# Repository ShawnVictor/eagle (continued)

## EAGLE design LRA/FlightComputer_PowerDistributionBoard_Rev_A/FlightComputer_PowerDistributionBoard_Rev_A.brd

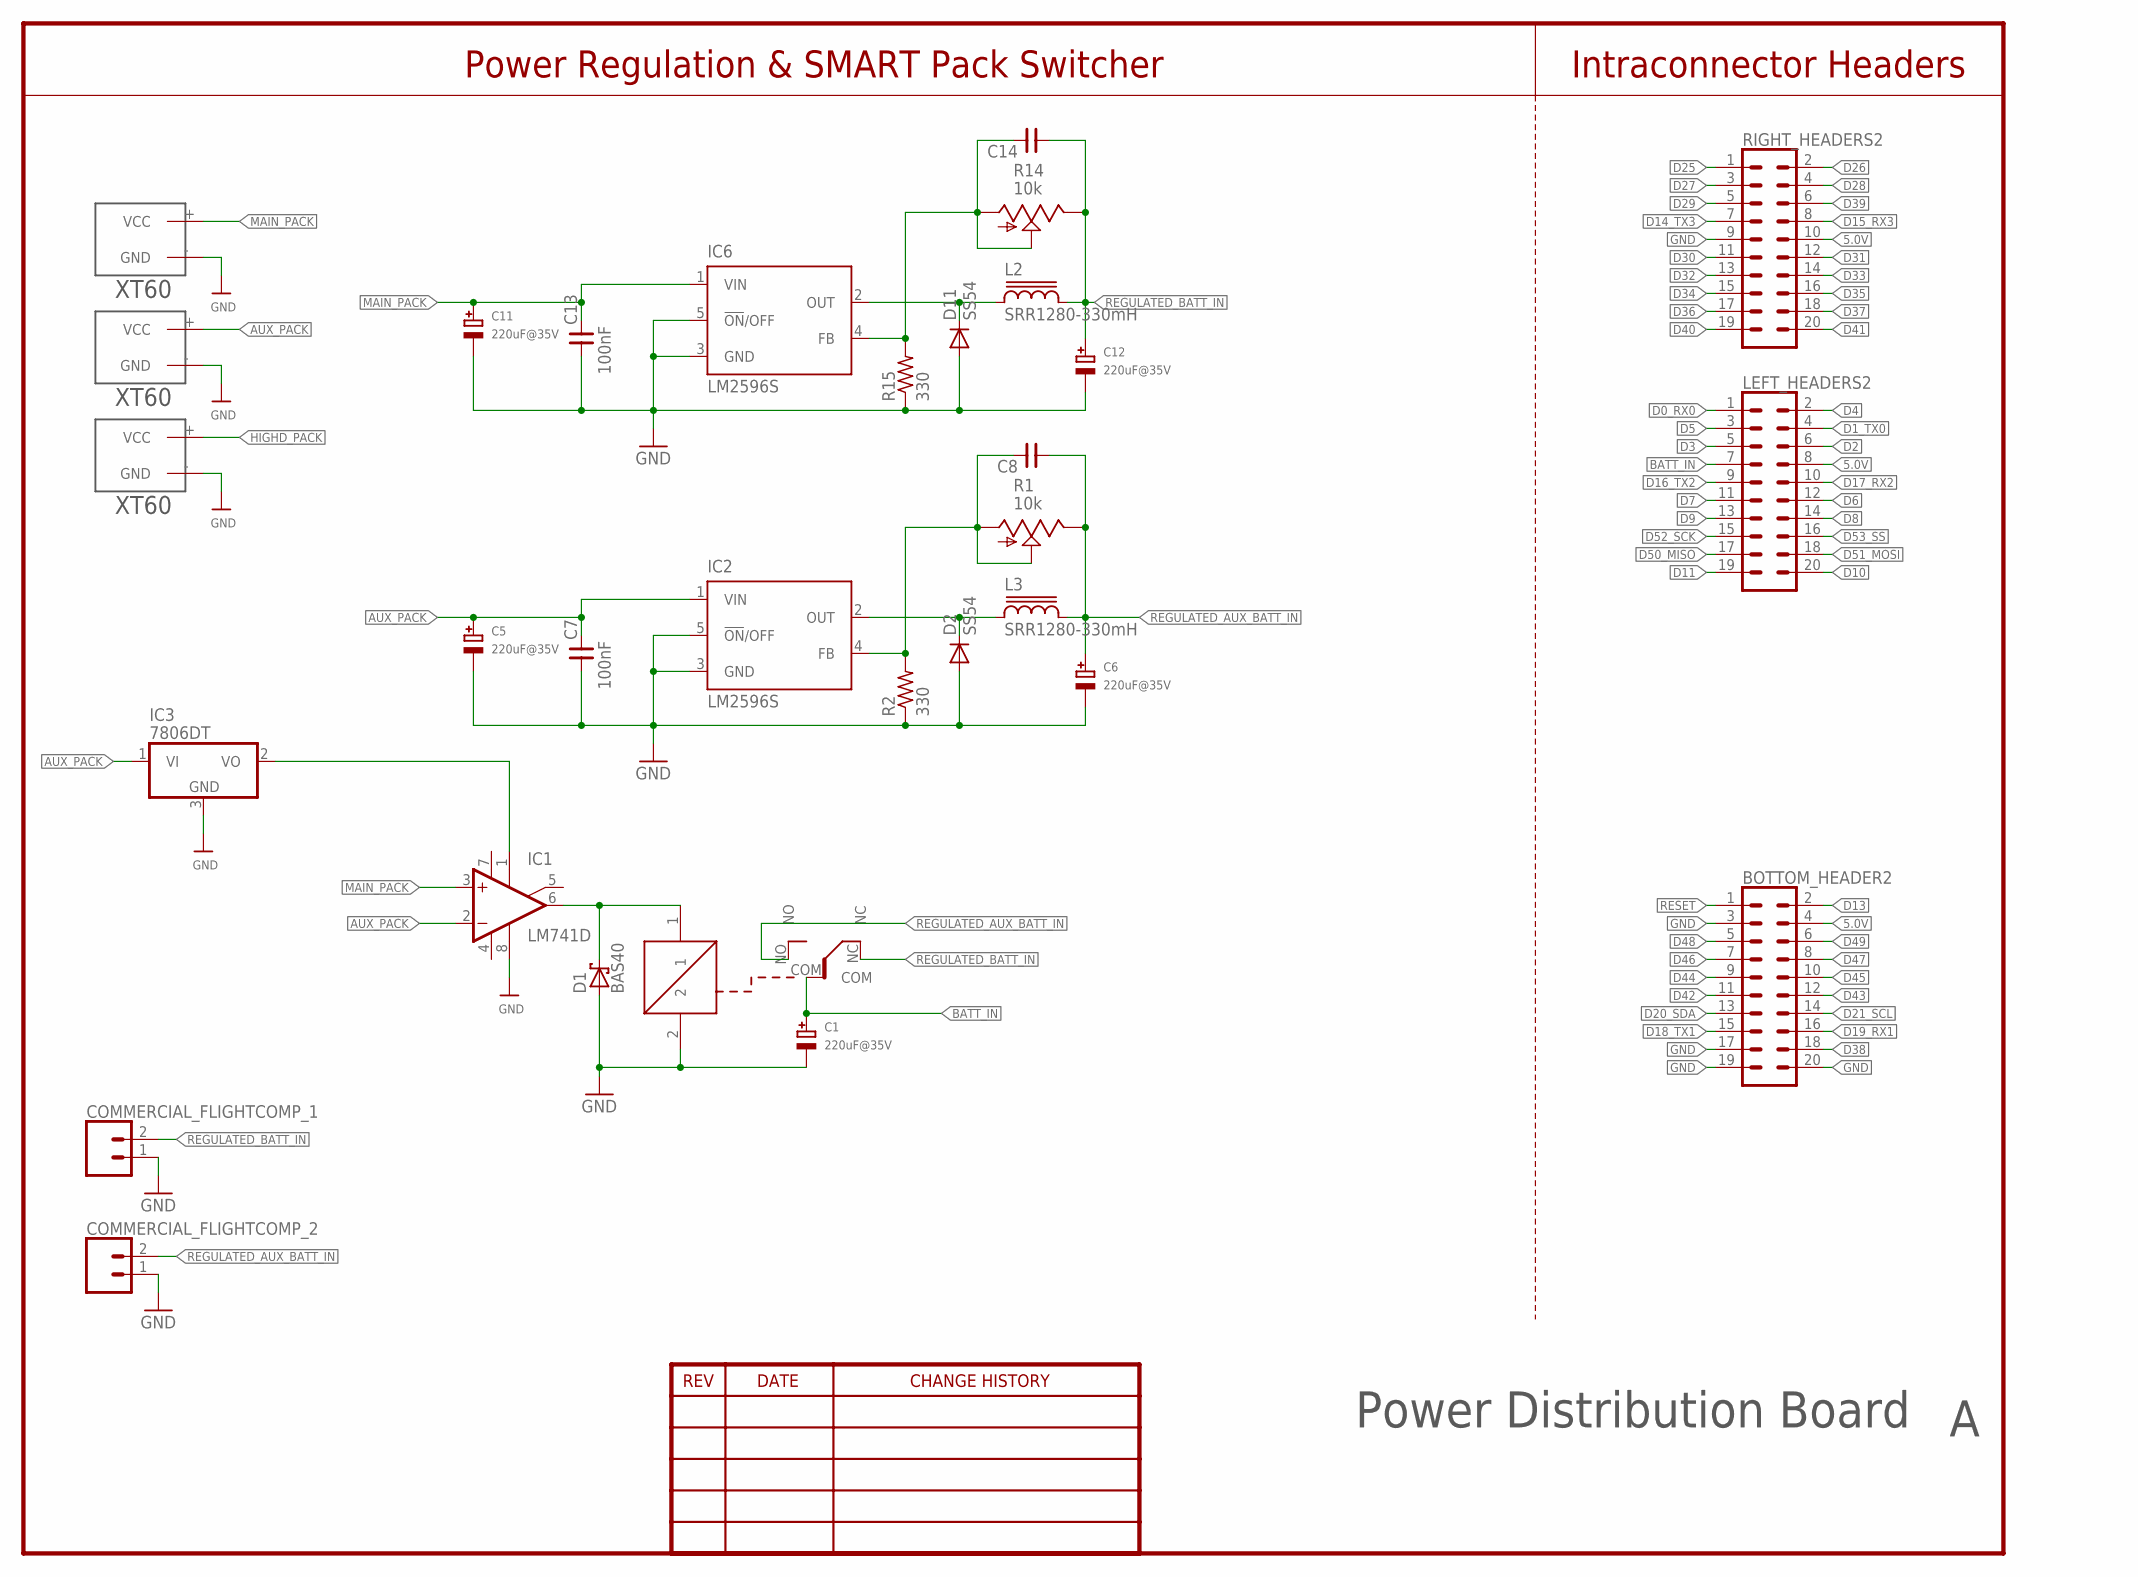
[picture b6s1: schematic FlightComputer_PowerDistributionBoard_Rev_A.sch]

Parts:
BOTTOM_HEADER2: CONN_10X2; 2X10
C1, C5, C6, C11, C12: 220uF@35V; PANASONIC_D
C7, C13: 100nF; 0603
C8, C14: CNP-0603; 0603
COMMERCIAL_FLIGHTCOMP_1, COMMERCIAL_FLIGHTCOMP_2: CONN_02; 1X02
D1: BAS40; SOT23
D2, D11: SS54; DO214AB
IC1: LM741D; SO08
IC2, IC6: LM2596S; TO263-5
IC3: 7806DT; TO252
L2, L3: SRR1280-330mH; SRR1280
LEFT_HEADERS2: CONN_10X2; 2X10
R1, R14: 10k; S64W
R2, R15: 330; R0603
RIGHT_HEADERS2: CONN_10X2; 2X10
U$2, U$3, U$4: XT60
U$14: RW-SH

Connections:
5.0V: BOTTOM_HEADER2.4, LEFT_HEADERS2.8, RIGHT_HEADERS2.10
AUX_PACK: C5.+, C7.2, IC1.2 (-IN), IC2.1 (VIN), IC3.1 (VI), U$3.+ (VCC)
BATT_IN: C1.+, LEFT_HEADERS2.7, U$14.COM
D0_RX0: LEFT_HEADERS2.1
D1_TX0: LEFT_HEADERS2.4
D2: LEFT_HEADERS2.6
D3: LEFT_HEADERS2.5
D4: LEFT_HEADERS2.2
D5: LEFT_HEADERS2.3
D6: LEFT_HEADERS2.12
D7: LEFT_HEADERS2.11
D8: LEFT_HEADERS2.14
D9: LEFT_HEADERS2.13
D10: LEFT_HEADERS2.20
D11: LEFT_HEADERS2.19
D13: BOTTOM_HEADER2.2
D14_TX3: RIGHT_HEADERS2.7
D15_RX3: RIGHT_HEADERS2.8
D16_TX2: LEFT_HEADERS2.9
D17_RX2: LEFT_HEADERS2.10
D18_TX1: BOTTOM_HEADER2.15
D19_RX1: BOTTOM_HEADER2.16
D20_SDA: BOTTOM_HEADER2.13
D21_SCL: BOTTOM_HEADER2.14
D25: RIGHT_HEADERS2.1
D26: RIGHT_HEADERS2.2
D27: RIGHT_HEADERS2.3
D28: RIGHT_HEADERS2.4
D29: RIGHT_HEADERS2.5
D30: RIGHT_HEADERS2.11
D31: RIGHT_HEADERS2.12
D32: RIGHT_HEADERS2.13
D33: RIGHT_HEADERS2.14
D34: RIGHT_HEADERS2.15
D35: RIGHT_HEADERS2.16
D36: RIGHT_HEADERS2.17
D37: RIGHT_HEADERS2.18
D38: BOTTOM_HEADER2.18
D39: RIGHT_HEADERS2.6
D40: RIGHT_HEADERS2.19
D41: RIGHT_HEADERS2.20
D42: BOTTOM_HEADER2.11
D43: BOTTOM_HEADER2.12
D44: BOTTOM_HEADER2.9
D45: BOTTOM_HEADER2.10
D46: BOTTOM_HEADER2.7
D47: BOTTOM_HEADER2.8
D48: BOTTOM_HEADER2.5
D49: BOTTOM_HEADER2.6
D50_MISO: LEFT_HEADERS2.17
D51_MOSI: LEFT_HEADERS2.18
D52_SCK: LEFT_HEADERS2.15
D53_SS: LEFT_HEADERS2.16
GND: BOTTOM_HEADER2.3, BOTTOM_HEADER2.17, BOTTOM_HEADER2.19, BOTTOM_HEADER2.20, C1.-, C5.-, C6.-, C7.1, C11.-, C12.-, C13.1, COMMERCIAL_FLIGHTCOMP_1.1, COMMERCIAL_FLIGHTCOMP_2.1, D1.1 (A), D2.A, D11.A, IC1.8 (OPT), IC2.3 (GND), IC2.5 (!ON!/OFF), IC3.3 (GND), IC6.3 (GND), IC6.5 (!ON!/OFF), R2.1, R15.1, RIGHT_HEADERS2.9, U$2.- (GND), U$3.- (GND), U$4.- (GND), U$14.2
HIGHD_PACK: U$4.+ (VCC)
MAIN_PACK: C11.+, C13.2, IC1.3 (+IN), IC6.1 (VIN), U$2.+ (VCC)
unnamed: D2.C, IC2.2 (OUT), L3.1
unnamed: C8.2, IC2.4 (FB), R1.A, R1.S, R2.2
unnamed: IC1.1 (ON1), IC3.2 (VO)
unnamed: D1.3 (C), IC1.6 (OUT), U$14.1
unnamed: D11.C, IC6.2 (OUT), L2.1
unnamed: C14.2, IC6.4 (FB), R14.A, R14.S, R15.2
REGULATED_AUX_BATT_IN: C6.+, C8.1, COMMERCIAL_FLIGHTCOMP_2.2, L3.2, R1.E, U$14.NO
REGULATED_BATT_IN: C12.+, C14.1, COMMERCIAL_FLIGHTCOMP_1.2, L2.2, R14.E, U$14.NC
RESET: BOTTOM_HEADER2.1
V+: IC1.7 (V+)
V-: IC1.4 (V-)

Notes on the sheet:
Intraconnector Headers
Power Regulation & SMART Pack Switcher
Power Distribution Board

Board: 2 copper layers, 31 parts (0 on the bottom side), 13 nets, no tracks yet.

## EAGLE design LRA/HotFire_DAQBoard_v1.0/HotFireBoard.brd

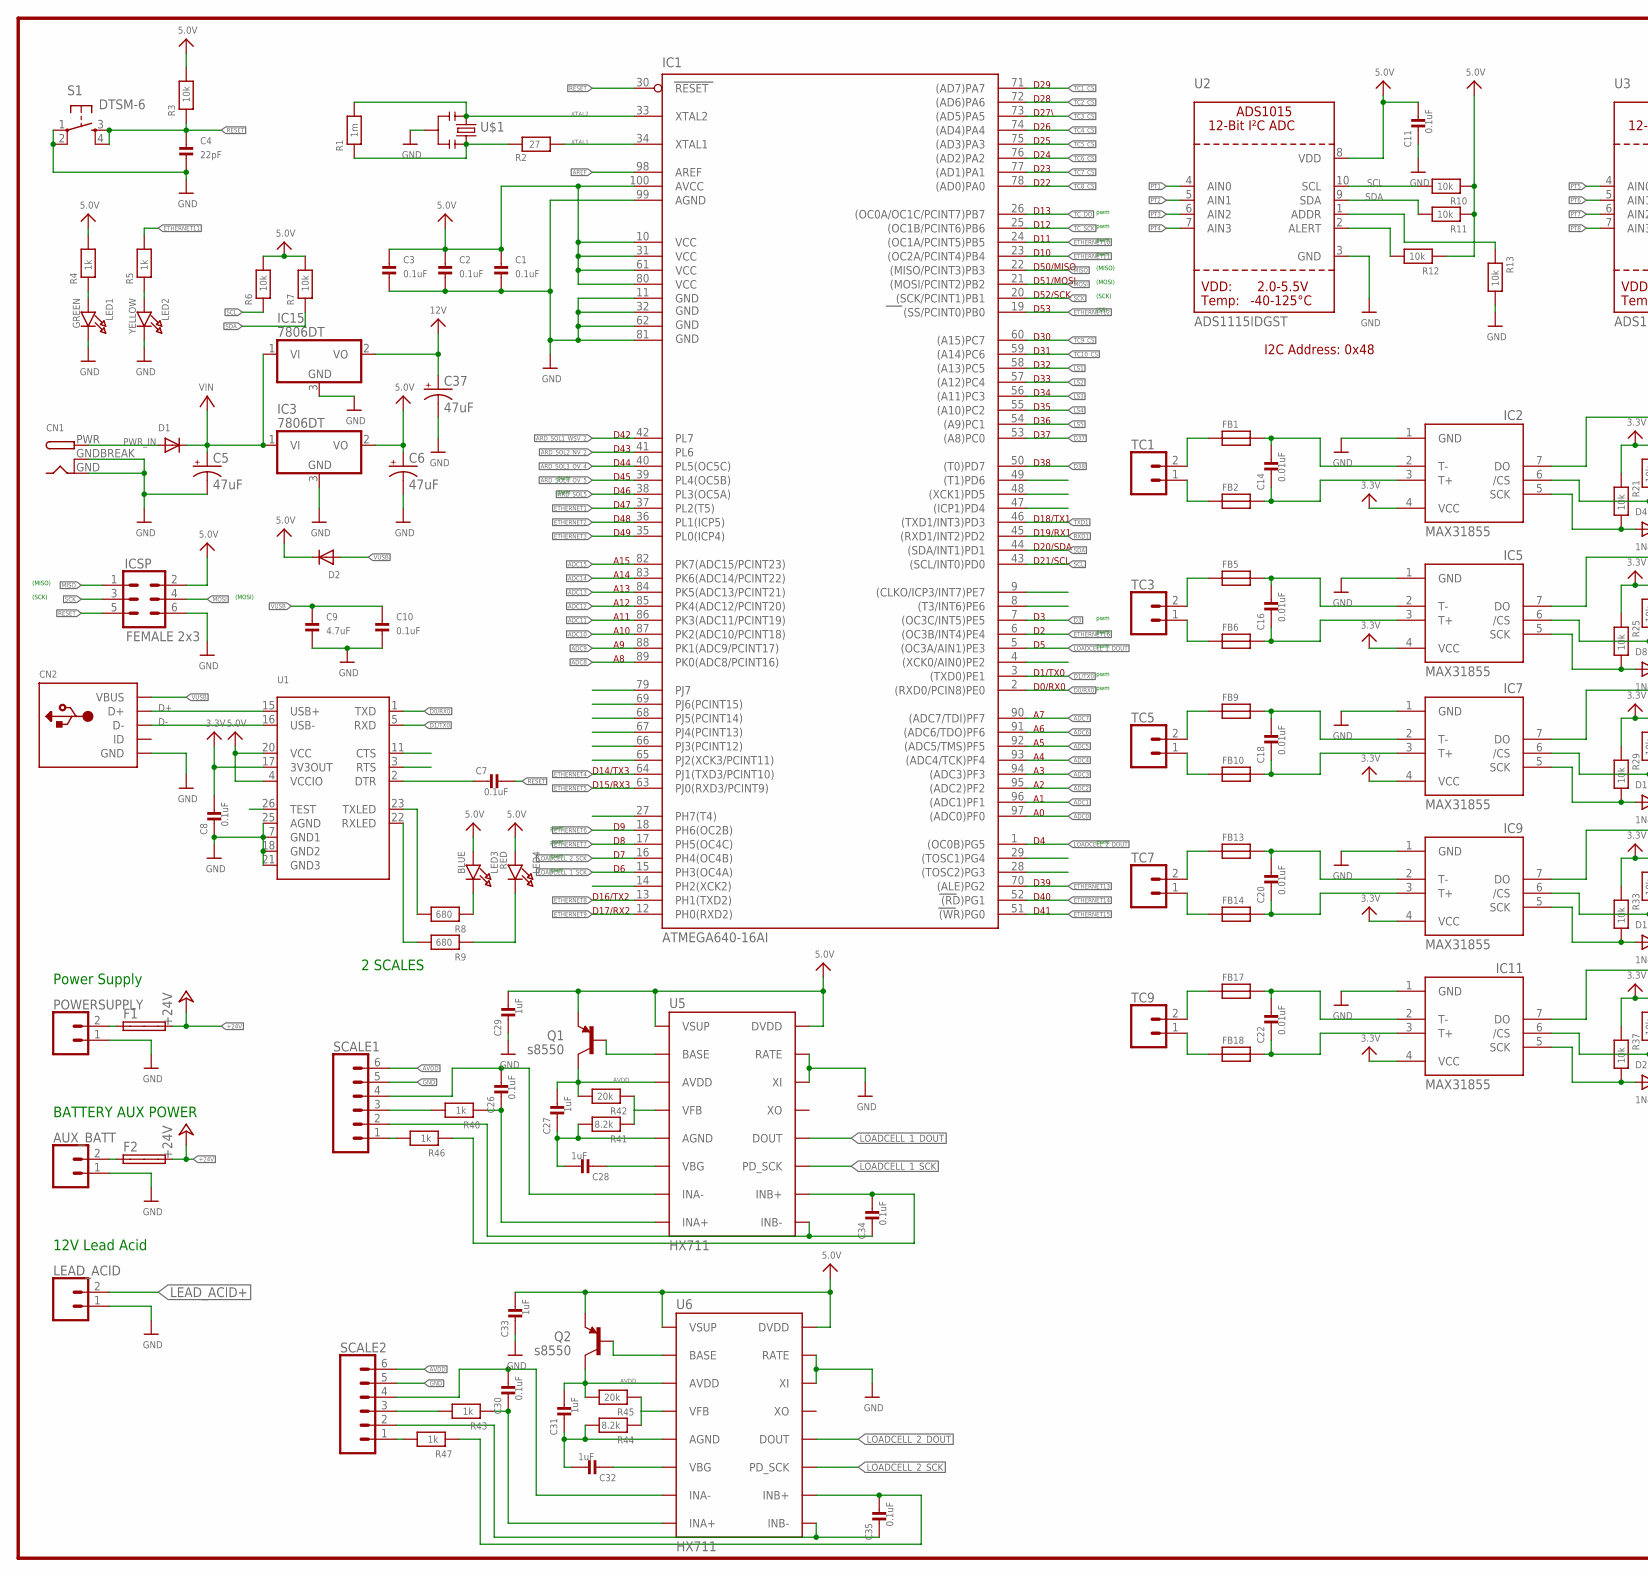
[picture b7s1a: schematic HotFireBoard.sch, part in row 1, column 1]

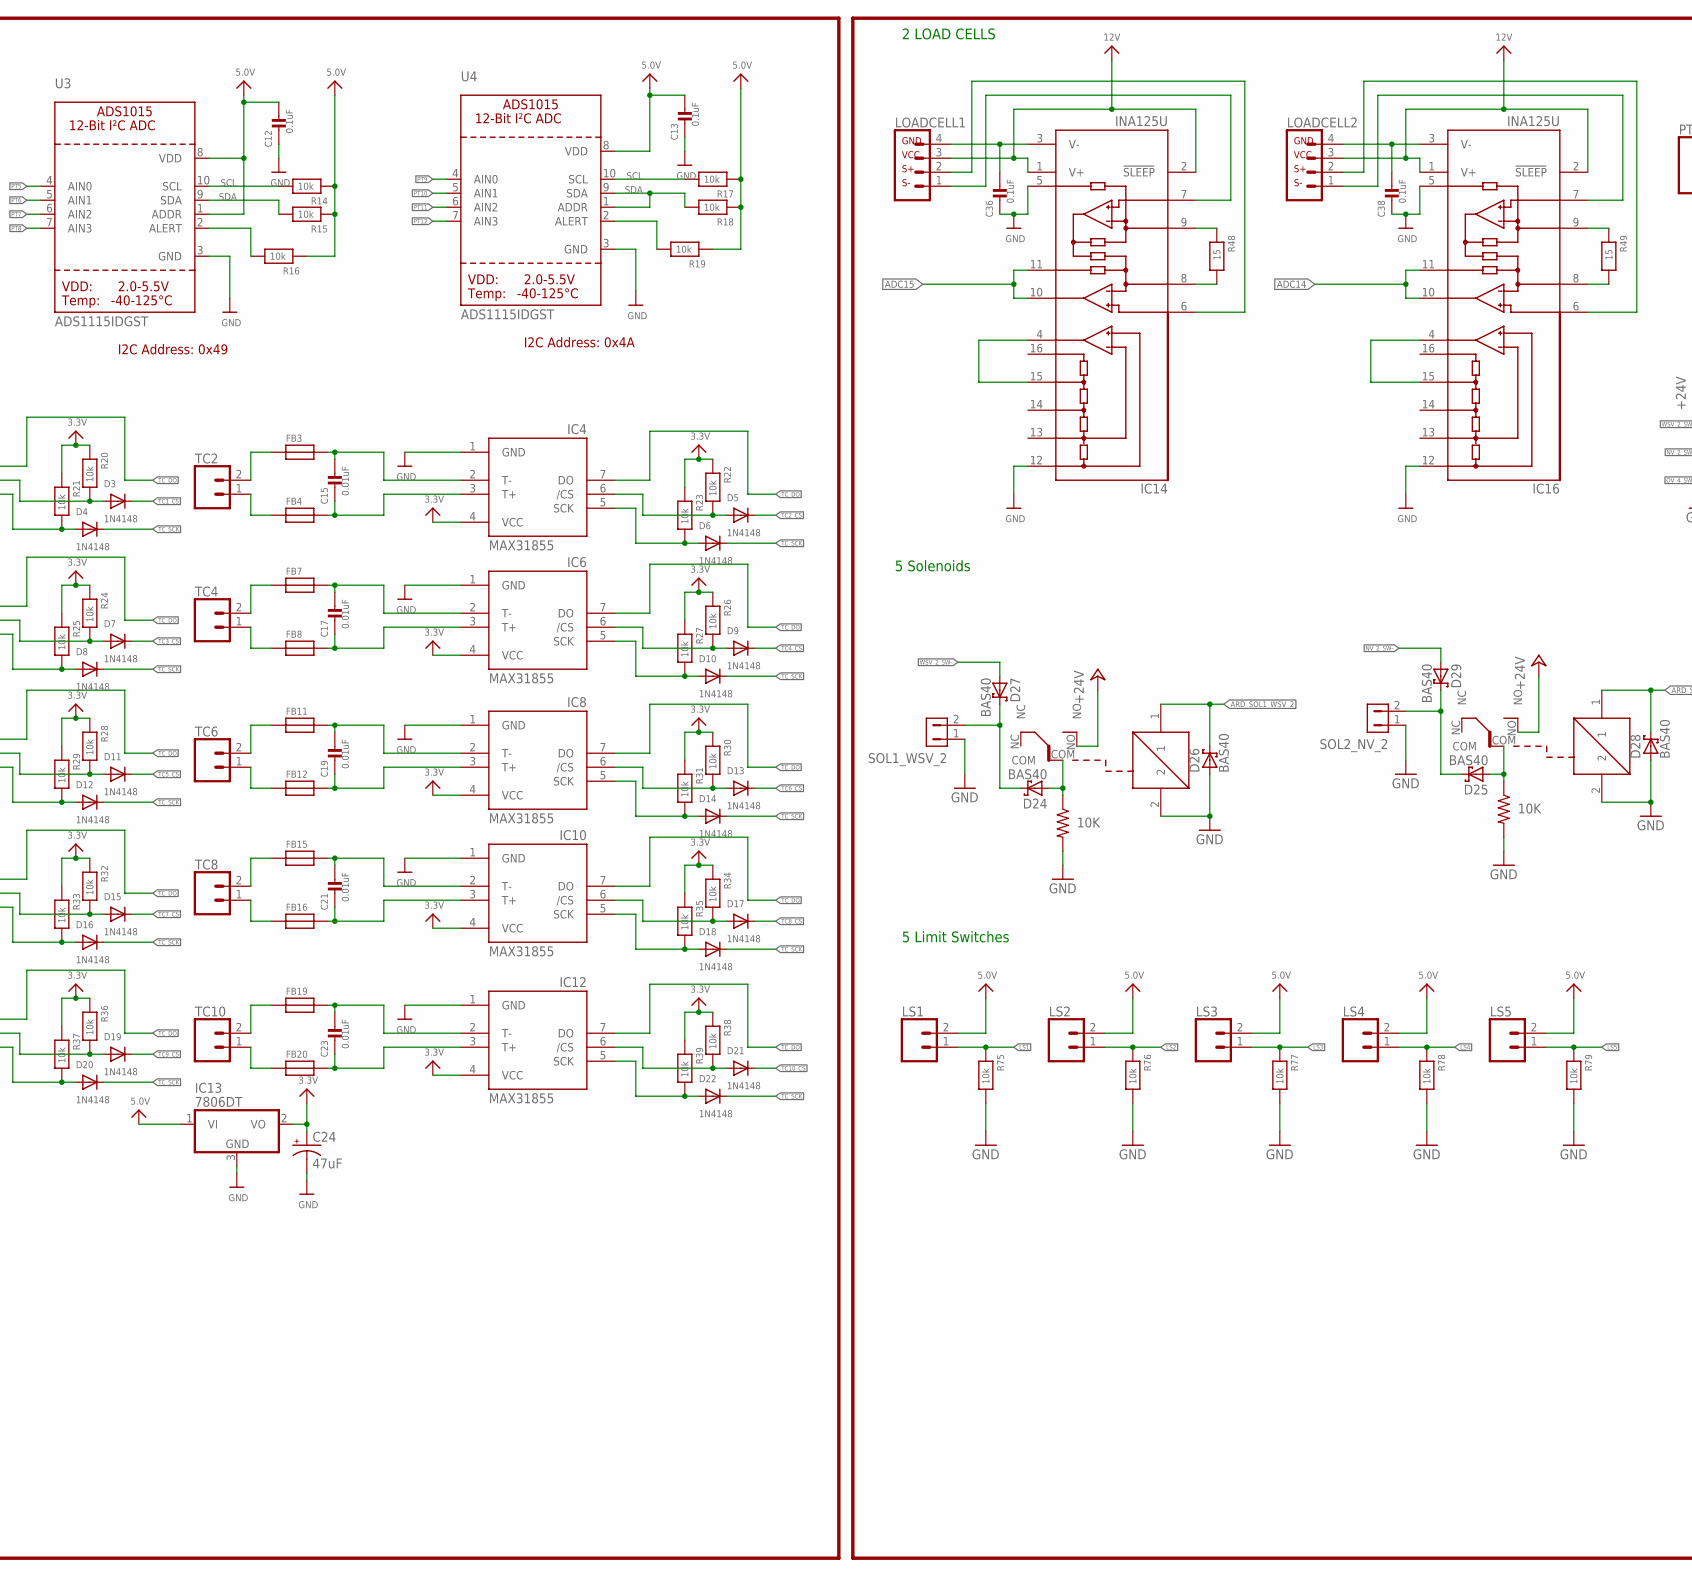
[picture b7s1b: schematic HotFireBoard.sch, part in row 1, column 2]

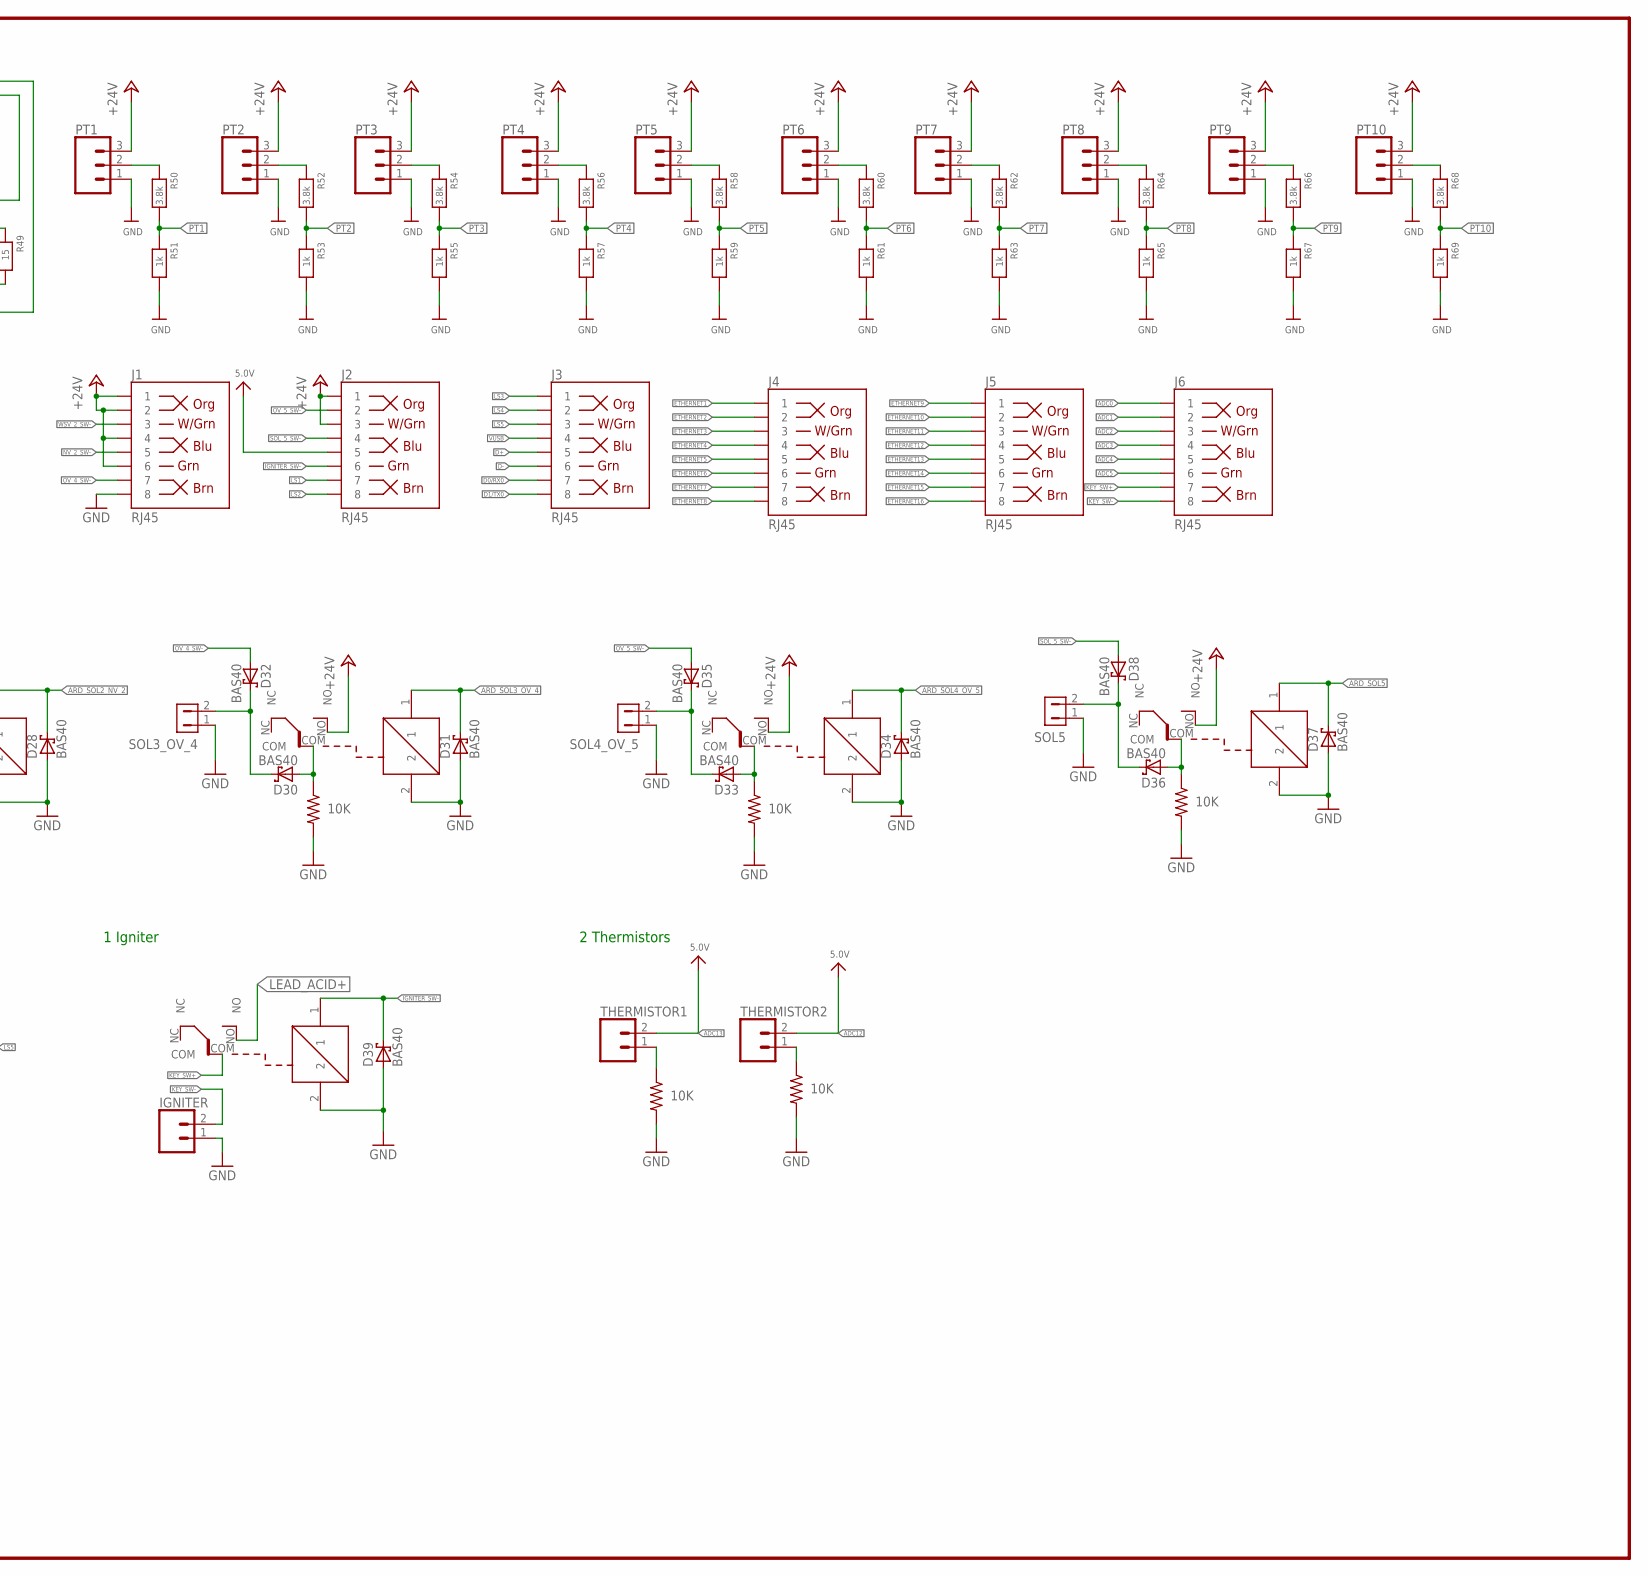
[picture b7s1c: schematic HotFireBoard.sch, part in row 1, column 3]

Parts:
AUX_BATT: CONN_02; 1X02
C1, C2, C3, C7, C8, C10, C11, C12, C13, C26, C30, C34, C35, C36, C38: 0.1uF; 0805
C4: 22pF; 0805
C5, C6, C24, C37: 47uF; PANASONIC_D
C9: 4.7uF; 0805
C14, C15, C16, C17, C18, C19, C20, C21, C22, C23: 0.01uF; 0805
C27, C28, C29, C31, C32, C33: 1uF; 0805
CN1: DCBARRELPTH; DCJACK_2MM_PTH
CN2: USBMINIB; USB-MINIB
D1, D2: DIODESOD-123; SOD-123
D3, D4, D5, D6, D7, D8, D9, D10, D11, D12, D13, D14, D15, D16, D17, D18, D19, D20, D21, D22: 1N4148; SOD-123
D24, D25, D26, D27, D28, D29, D30, D31, D32, D33, D34, D35, D36, D37, D38, D39: BAS40; SOT23
F1, F2: SHK20L
FB1, FB2, FB3, FB4, FB5, FB6, FB7, FB8, FB9, FB10, FB11, FB12, FB13, FB14, FB15, FB16, FB17, FB18, FB19, FB20: FERRITE; 0603
IC1: ATMEGA640-16AI; TQFP100
IC2, IC4, IC5, IC6, IC7, IC8, IC9, IC10, IC11, IC12: MAX31855; SO08
IC3, IC13, IC15: 7806DT; TO252
IC14, IC16: INA125U; SO16-1
ICSP: FEMALE 2x3; 2X3
IGNITER: CONN_025MM; SCREWTERMINAL-5MM-2
J1, J2, J3, J4, J5, J6: RJ45; RJ45-8
LEAD_ACID: CONN_02; 1X02
LED1: GREEN; CHIPLED_0805
LED2: YELLOW; CHIPLED_0805
LED3: BLUE; CHIPLED_0805
LED4: RED; CHIPLED_0805
LOADCELL1, LOADCELL2: CONN_04; 1X04
LS1, LS2, LS3, LS4, LS5: CONN_02; 1X02
POWERSUPPLY: CONN_02; 1X02
PT1, PT2, PT3, PT4, PT5, PT6, PT7, PT8, PT9, PT10: CONN_03; 1X03
Q1, Q2: s8550; TO-92
R1: 1m; 0805
R2: 27; 0805
R3, R6, R7, R10, R11, R12, R13, R14, R15, R16, R17, R18, R19, R20, R21, R22, R23, R24, R25, R26, R27, R28, R29, R30, R31, R32, R33, R34, R35, R36, R37, R38, R39, R75, R76, R77, R78, R79: 10k; 0805
R4, R5, R40, R43, R46, R47, R51, R53, R55, R57, R59, R61, R63, R65, R67, R69: 1k; 0805
R8, R9: 680; 0805
R41, R44: 8.2k; 0805
R42, R45: 20k; 0805
R48, R49: 15; 0805
R50, R52, R54, R56, R58, R60, R62, R64, R66, R68: 3.8k; 0805
R70, R71, R72, R73, R74, R80, R81: 10K; M0805
S1: DTSM-6
SCALE1, SCALE2: CONN_06SILK_FEMALE_PTH; 1X06
SOL1_WSV_2, SOL2_NV_2, SOL3_OV_4, SOL4_OV_5, SOL5: HDR-1X2-MTA-100; MTA-100-2V
TC1, TC2, TC3, TC4, TC5, TC6, TC7, TC8, TC9, TC10: CONN_02; 1X02
THERMISTOR1, THERMISTOR2: CONN_02; 1X02
U1: FT232RLSSOP28; SSOP28DB
U2, U3, U4: ADS1115IDGST; MSOP10
U5, U6: HX711; SO16
U$1: RESONATORSMD; RESONATOR-SMD
U$128, U$129, U$130, U$131, U$132, U$138: RW-SH

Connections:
3.3V: C8.2, C24.+, IC2.4 (VCC), IC4.4 (VCC), IC5.4 (VCC), IC6.4 (VCC), IC7.4 (VCC), IC8.4 (VCC), IC9.4 (VCC), IC10.4 (VCC), IC11.4 (VCC), IC12.4 (VCC), IC13.2 (VO), R20.1, R21.1, R22.1, R23.1, R24.1, R25.1, R26.1, R27.1, R28.1, R29.1, R30.1, R31.1, R32.1, R33.1, R34.1, R35.1, R36.1, R37.1, R38.1, R39.1, U1.17 (3V3OUT)
5.0V: C1.1, C2.1, C3.1, C6.+, C11.2, C12.2, C13.2, C29.2, C33.2, D2.C, IC1.10 (VCC), IC1.31 (VCC1), IC1.61 (VCC2), IC1.80 (VCC3), IC1.100 (AVCC), IC3.2 (VO), IC13.1 (VI), ICSP.2, J2.5, LED3.A, LED4.A, LS1.2, LS2.2, LS3.2, LS4.2, LS5.2, Q1.1 (E), Q2.1 (E), R3.2, R4.2, R6.2, R7.2, R10.1, R11.1, R12.1, R14.1, R15.1, R16.1, R17.1, R18.1, R19.1, U1.4 (VCCIO), U1.20 (VCC), U2.8 (VDD), U3.1 (ADDR), U3.8 (VDD), U4.8 (VDD), U5.1 (VSUP), U5.16 (DVDD), U6.1 (VSUP), U6.16 (DVDD)
12V: C37.+, IC14.1 (V+), IC14.2 (!SLEEP), IC15.2 (VO), IC16.1 (V+), IC16.2 (!SLEEP), LOADCELL1.3, LOADCELL2.3
+24V: F1.2A, F2.2A, J1.1, J1.2, J1.4, J1.6, J2.1, J2.3, PT1.3, PT2.3, PT3.3, PT4.3, PT5.3, PT6.3, PT7.3, PT8.3, PT9.3, PT10.3, U$128.NO, U$129.NO, U$130.NO, U$131.NO, U$132.NO
ADC0: IC1.97 ((ADC0)PF0), J6.1
ADC1: IC1.96 ((ADC1)PF1), J6.2
ADC2: IC1.95 ((ADC2)PF2), J6.3
ADC3: IC1.94 ((ADC3)PF3), J6.4
ADC4: IC1.93 ((ADC4/TCK)PF4), J6.5
ADC5: IC1.92 ((ADC5/TMS)PF5), J6.6
ADC6: IC1.91 ((ADC6/TDO)PF6)
ADC7: IC1.90 ((ADC7/TDI)PF7)
ADC8: IC1.89 (PK0(ADC8/PCINT16))
ADC9: IC1.88 (PK1(ADC9/PCINT17))
ADC10: IC1.87 (PK2(ADC10/PCINT18))
ADC11: IC1.86 (PK3(ADC11/PCINT19))
ADC12: IC1.85 (PK4(ADC12/PCINT20)), THERMISTOR2.2
ADC13: IC1.84 (PK5(ADC13/PCINT21)), THERMISTOR1.2
ADC14: IC1.83 (PK6(ADC14/PCINT22)), IC16.10 (OUT), IC16.11 (SENSE)
ADC15: IC1.82 (PK7(ADC15/PCINT23)), IC14.10 (OUT), IC14.11 (SENSE)
ARD_SOL1_WSV_2: D26.3 (C), IC1.42 (PL7), U$128.1
ARD_SOL2_NV_2: D28.3 (C), IC1.41 (PL6), U$129.1
ARD_SOL3_OV_4: D31.3 (C), IC1.40 (PL5(OC5C)), U$130.1
ARD_SOL4_OV_5: D34.3 (C), IC1.39 (PL4(OC5B)), U$131.1
ARD_SOL5: D37.3 (C), IC1.38 (PL3(OC5A)), U$132.1
AREF: IC1.98 (AREF)
AVDD: C27.2, C31.2, Q1.3 (C), Q2.3 (C), R42.2, R45.2, SCALE1.6, SCALE2.6, U5.3 (AVDD), U6.3 (AVDD)
D0/RX0: IC1.2 ((RXD0/PCIN8)PE0), J3.7, U1.1 (TXD)
D1/TX0: IC1.3 ((TXD0)PE1), J3.8, U1.5 (RXD)
D3: IC1.7 ((OC3C/INT5)PE5)
D37: IC1.53 ((A8)PC0)
D38: IC1.50 ((T0)PD7)
D+: CN2.D+, J3.5, U1.15 (USB+)
D-: CN2.D-, J3.6, U1.16 (USB-)
ETHERNET1: IC1.37 (PL2(T5)), J4.1
ETHERNET2: IC1.36 (PL1(ICP5)), J4.2
ETHERNET3: IC1.35 (PL0(ICP4)), J4.3
ETHERNET4: IC1.64 (PJ1(TXD3/PCINT10)), J4.4
ETHERNET5: IC1.63 (PJ0(RXD3/PCINT9)), J4.5
ETHERNET6: IC1.18 (PH6(OC2B)), J4.6
ETHERNET7: IC1.17 (PH5(OC4C)), J4.7
ETHERNET8: IC1.13 (PH1(TXD2)), J4.8
ETHERNET9: IC1.12 (PH0(RXD2)), J5.1
ETHERNET10: IC1.24 ((OC1A/PCINT5)PB5), J5.2
ETHERNET11: IC1.23 ((OC2A/PCINT4)PB4), J5.3, R5.2
ETHERNET12: IC1.19 ((SS/PCINT0)PB0), J5.4
ETHERNET13: IC1.70 ((ALE)PG2), J5.5
ETHERNET14: IC1.52 ((RD)PG1), J5.6
ETHERNET15: IC1.51 ((WR)PG0), J5.7
ETHERNET16: IC1.6 ((OC3B/INT4)PE4), J5.8
GND: AUX_BATT.1, C1.2, C2.2, C3.2, C4.2, C5.-, C6.-, C8.1, C9.1, C10.1, C11.1, C12.1, C13.1, C24.-, C29.1, C33.1, C36.1, C37.-, C38.1, CN1.GND, CN1.GNDBREAK, CN2.GND, D26.1 (A), D28.1 (A), D31.1 (A), D34.1 (A), D37.1 (A), D39.1 (A), IC1.11 (GND), IC1.32 (GND1), IC1.62 (GND2), IC1.81 (GND3), IC1.99 (AGND), IC2.1 (GND), IC3.3 (GND), IC4.1 (GND), IC5.1 (GND), IC6.1 (GND), IC7.1 (GND), IC8.1 (GND), IC9.1 (GND), IC10.1 (GND), IC11.1 (GND), IC12.1 (GND), IC13.3 (GND), IC14.5 (REF), IC14.12 (REFCOM), IC15.3 (GND), IC16.5 (REF), IC16.12 (REFCOM), ICSP.6, IGNITER.1, J1.8, LEAD_ACID.1, LED1.C, LED2.C, POWERSUPPLY.1, PT1.1, PT2.1, PT3.1, PT4.1, PT5.1, PT6.1, PT7.1, PT8.1, PT9.1, PT10.1, R13.2, R51.2, R53.2, R55.2, R57.2, R59.2, R61.2, R63.2, R65.2, R67.2, R69.2, R70.2, R71.2, R72.2, R73.2, R74.2, R75.2, R76.2, R77.2, R78.2, R79.2, R80.2, R81.2, S1.1, S1.2, SCALE1.5, SCALE2.5, SOL1_WSV_2.1, SOL2_NV_2.1, SOL3_OV_4.1, SOL4_OV_5.1, SOL5.1, U1.7 (GND1), U1.18 (GND2), U1.21 (GND3), U1.25 (AGND), U2.3 (GND), U3.3 (GND), U4.3 (GND), U5.14 (XI), U5.15 (RATE), U6.14 (XI), U6.15 (RATE), U$1.2, U$128.2, U$129.2, U$130.2, U$131.2, U$132.2, U$138.2
IGNITER_SW-: D39.3 (C), J2.6, U$138.1
KEY_SW+: J6.7, U$138.COM
KEY_SW-: IGNITER.2, J6.8
LEAD_ACID+: LEAD_ACID.2, U$138.NO
LOADCELL_1_DOUT: IC1.5 ((OC3A/AIN1)PE3), U5.12 (DOUT)
LOADCELL_1_SCK: IC1.15 (PH3(OC4A)), U5.11 (PD_SCK)
LOADCELL_2_DOUT: IC1.1 ((OC0B)PG5), U6.12 (DOUT)
LOADCELL_2_SCK: IC1.16 (PH4(OC4B)), U6.11 (PD_SCK)
LS1: IC1.58 ((A13)PC5), J2.7, LS1.1, R75.1
LS2: IC1.57 ((A12)PC4), J2.8, LS2.1, R76.1
LS3: IC1.56 ((A11)PC3), J3.1, LS3.1, R77.1
LS4: IC1.55 ((A10)PC2), J3.2, LS4.1, R78.1
LS5: IC1.54 ((A9)PC1), J3.3, LS5.1, R79.1
MISO: IC1.22 ((MISO/PCINT3)PB3), ICSP.1
MOSI: IC1.21 ((MOSI/PCINT2)PB2), ICSP.4
unnamed: R1.1, R2.2, U$1.3
unnamed: F1.1A, POWERSUPPLY.2
unnamed: AUX_BATT.2, F2.1A
unnamed: LED1.A, R4.1
unnamed: LED2.A, R5.1
unnamed: LED3.C, R8.1
unnamed: R9.2, U1.22 (RXLED)
unnamed: R8.2, U1.23 (TXLED)
unnamed: LED4.C, R9.1
unnamed: C14.1, FB2.2, IC2.3 (T+)
unnamed: C7.1, U1.2 (DTR)
unnamed: C14.2, FB1.2, IC2.2 (T-)
unnamed: D3.A, IC2.6 (/CS), R20.2
unnamed: R12.2, U2.2 (ALERT)
unnamed: R16.2, U3.2 (ALERT)
unnamed: R13.1, U2.1 (ADDR)
unnamed: FB1.1, TC1.2
unnamed: R19.2, U4.2 (ALERT)
unnamed: FB2.1, TC1.1
unnamed: D4.A, IC2.5 (SCK), R21.2
unnamed: C15.2, FB3.2, IC4.2 (T-)
unnamed: C15.1, FB4.2, IC4.3 (T+)
unnamed: FB3.1, TC2.2
unnamed: FB4.1, TC2.1
unnamed: D5.A, IC4.6 (/CS), R22.2
unnamed: D6.A, IC4.5 (SCK), R23.2
unnamed: C16.2, FB5.2, IC5.2 (T-)
unnamed: C16.1, FB6.2, IC5.3 (T+)
unnamed: FB5.1, TC3.2
unnamed: FB6.1, TC3.1
unnamed: D7.A, IC5.6 (/CS), R24.2
unnamed: D8.A, IC5.5 (SCK), R25.2
unnamed: C17.2, FB7.2, IC6.2 (T-)
unnamed: C17.1, FB8.2, IC6.3 (T+)
unnamed: FB7.1, TC4.2
unnamed: FB8.1, TC4.1
unnamed: D9.A, IC6.6 (/CS), R26.2
unnamed: D10.A, IC6.5 (SCK), R27.2
unnamed: C18.2, FB9.2, IC7.2 (T-)
unnamed: C18.1, FB10.2, IC7.3 (T+)
unnamed: FB9.1, TC5.2
unnamed: FB10.1, TC5.1
unnamed: D11.A, IC7.6 (/CS), R28.2
unnamed: D12.A, IC7.5 (SCK), R29.2
unnamed: C19.2, FB11.2, IC8.2 (T-)
unnamed: C19.1, FB12.2, IC8.3 (T+)
unnamed: FB11.1, TC6.2
unnamed: FB12.1, TC6.1
unnamed: D13.A, IC8.6 (/CS), R30.2
unnamed: D14.A, IC8.5 (SCK), R31.2
unnamed: C20.2, FB13.2, IC9.2 (T-)
unnamed: C20.1, FB14.2, IC9.3 (T+)
unnamed: FB13.1, TC7.2
unnamed: FB14.1, TC7.1
unnamed: D15.A, IC9.6 (/CS), R32.2
unnamed: D16.A, IC9.5 (SCK), R33.2
unnamed: C21.2, FB15.2, IC10.2 (T-)
unnamed: C21.1, FB16.2, IC10.3 (T+)
unnamed: FB15.1, TC8.2
unnamed: FB16.1, TC8.1
unnamed: D17.A, IC10.6 (/CS), R34.2
unnamed: D18.A, IC10.5 (SCK), R35.2
unnamed: C22.2, FB17.2, IC11.2 (T-)
unnamed: C22.1, FB18.2, IC11.3 (T+)
unnamed: FB17.1, TC9.2
unnamed: FB18.1, TC9.1
unnamed: D19.A, IC11.6 (/CS), R36.2
unnamed: D20.A, IC11.5 (SCK), R37.2
unnamed: C23.2, FB19.2, IC12.2 (T-)
unnamed: C23.1, FB20.2, IC12.3 (T+)
unnamed: FB19.1, TC10.2
unnamed: FB20.1, TC10.1
unnamed: D21.A, IC12.6 (/CS), R38.2
unnamed: D22.A, IC12.5 (SCK), R39.2
unnamed: R40.2, SCALE1.3
unnamed: C26.1, R40.1, U5.8 (INA+)
unnamed: C26.2, SCALE1.4, U5.7 (INA-)
unnamed: R43.2, SCALE2.3
unnamed: C27.1, C28.2, R41.2, U5.5 (AGND)
unnamed: C28.1, U5.6 (VBG)
unnamed: R41.1, R42.1, U5.4 (VFB)
unnamed: Q1.2 (B), U5.2 (BASE)
unnamed: C30.1, R43.1, U6.8 (INA+)
unnamed: C30.2, SCALE2.4, U6.7 (INA-)
unnamed: C31.1, C32.2, R44.2, U6.5 (AGND)
unnamed: C32.1, U6.6 (VBG)
unnamed: R44.1, R45.1, U6.4 (VFB)
unnamed: Q2.2 (B), U6.2 (BASE)
unnamed: C34.1, SCALE1.2, U5.9 (INB-)
unnamed: C34.2, R46.1, U5.10 (INB+)
unnamed: R46.2, SCALE1.1
unnamed: C35.1, SCALE2.2, U6.9 (INB-)
unnamed: C35.2, R47.1, U6.10 (INB+)
unnamed: R47.2, SCALE2.1
unnamed: C36.2, IC14.3 (V-), LOADCELL1.4
unnamed: C38.2, IC16.3 (V-), LOADCELL2.4
unnamed: IC14.9 (RG), R48.1
unnamed: IC14.8 (RG), R48.2
unnamed: IC14.6 (+IN), LOADCELL1.2
unnamed: IC16.9 (RG), R49.1
unnamed: IC16.8 (RG), R49.2
unnamed: IC16.6 (+IN), LOADCELL2.2
unnamed: IC14.4 (REFOUT), IC14.15 (REF5)
unnamed: IC14.7 (-IN), LOADCELL1.1
unnamed: IC16.4 (REFOUT), IC16.15 (REF5)
unnamed: IC16.7 (-IN), LOADCELL2.1
unnamed: PT1.2, R50.1
unnamed: PT2.2, R52.1
unnamed: PT3.2, R54.1
unnamed: PT4.2, R56.1
unnamed: PT5.2, R58.1
unnamed: PT6.2, R60.1
unnamed: PT7.2, R62.1
unnamed: PT8.2, R64.1
unnamed: PT9.2, R66.1
unnamed: PT10.2, R68.1
unnamed: D24.3 (C), D27.3 (C), SOL1_WSV_2.2
unnamed: D24.1 (A), R70.1, U$128.COM
unnamed: D25.3 (C), D29.3 (C), SOL2_NV_2.2
unnamed: D25.1 (A), R71.1, U$129.COM
unnamed: D30.3 (C), D32.3 (C), SOL3_OV_4.2
unnamed: D30.1 (A), R72.1, U$130.COM
unnamed: D33.3 (C), D35.3 (C), SOL4_OV_5.2
unnamed: D33.1 (A), R73.1, U$131.COM
unnamed: D36.3 (C), D38.3 (C), SOL5.2
unnamed: D36.1 (A), R74.1, U$132.COM
unnamed: R80.1, THERMISTOR1.1
unnamed: R81.1, THERMISTOR2.1
NV_2_SW-: D29.1 (A), J1.5
OV_4_SW-: D32.1 (A), J1.7
OV_5_SW-: D35.1 (A), J2.2
PT1: R50.2, R51.1, U2.4 (AIN0)
PT2: R52.2, R53.1, U2.5 (AIN1)
PT3: R54.2, R55.1, U2.6 (AIN2)
PT4: R56.2, R57.1, U2.7 (AIN3)
PT5: R58.2, R59.1, U3.4 (AIN0)
PT6: R60.2, R61.1, U3.5 (AIN1)
PT7: R62.2, R63.1, U3.6 (AIN2)
PT8: R64.2, R65.1, U3.7 (AIN3)
PT9: R66.2, R67.1, U4.4 (AIN0)
PT10: R68.2, R69.1, U4.5 (AIN1)
PT11: U4.6 (AIN2)
PT12: U4.7 (AIN3)
PWR_IN: CN1.PWR, D1.A
RESET: C4.1, C7.2, IC1.30 (RESET), ICSP.5, R3.1, S1.3, S1.4
RXD1: IC1.45 ((RXD1/INT2)PD2)
SCK: IC1.20 ((SCK/PCINT1)PB1), ICSP.3
SCL: IC1.43 ((SCL/INT0)PD0), R6.1, R10.2, R14.2, R17.2, U2.10 (SCL), U3.10 (SCL), U4.10 (SCL)
SDA: IC1.44 ((SDA/INT1)PD1), R7.1, R11.2, R15.2, R18.2, U2.9 (SDA), U3.9 (SDA), U4.1 (ADDR), U4.9 (SDA)
SOL_5_SW-: D38.1 (A), J2.4
TC1_CS: D3.C, IC1.71 ((AD7)PA7)
TC2_CS: D5.C, IC1.72 ((AD6)PA6)
TC3_CS: D7.C, IC1.73 ((AD5)PA5)
TC4_CS: D9.C, IC1.74 ((AD4)PA4)
TC5_CS: D11.C, IC1.75 ((AD3)PA3)
TC6_CS: D13.C, IC1.76 ((AD2)PA2)
TC7_CS: D15.C, IC1.77 ((AD1)PA1)
TC8_CS: D17.C, IC1.78 ((AD0)PA0)
TC9_CS: D19.C, IC1.60 ((A15)PC7)
TC10_CS: D21.C, IC1.59 ((A14)PC6)
TC_DO: IC1.26 ((OC0A/OC1C/PCINT7)PB7), IC2.7 (DO), IC4.7 (DO), IC5.7 (DO), IC6.7 (DO), IC7.7 (DO), IC8.7 (DO), IC9.7 (DO), IC10.7 (DO), IC11.7 (DO), IC12.7 (DO)
TC_SCK: D4.C, D6.C, D8.C, D10.C, D12.C, D14.C, D16.C, D18.C, D20.C, D22.C, IC1.25 ((OC1B/PCINT6)PB6)
TXD1: IC1.46 ((TXD1/INT3)PD3)
VIN: C5.+, D1.C, IC3.1 (VI), IC15.1 (VI)
VUSB: C9.2, C10.2, CN2.VBUS, D2.A, J3.4
WSV_2_SW-: D27.1 (A), J1.3
XTAL1: IC1.34 (XTAL1), R2.1
XTAL2: IC1.33 (XTAL2), R1.2, U$1.1

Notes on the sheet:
pwm
(SS)
(SCK)
(MOSI)
(MISO)
I2C Address: 0x48
I2C Address: 0x49
I2C Address: 0x4A
BATTERY AUX POWER
5 Solenoids
5 Limit Switches
1 Igniter
2 SCALES
2 Thermistors
GND
VCC
2 LOAD CELLS
D42
D43
D44
D45
D46
D47
D48
D49
A15
A14
A13
A12
A11
A10
D14/TX3
D15/RX3
D16/TX2
D17/RX2
D29
D28
D27\
D26
D25

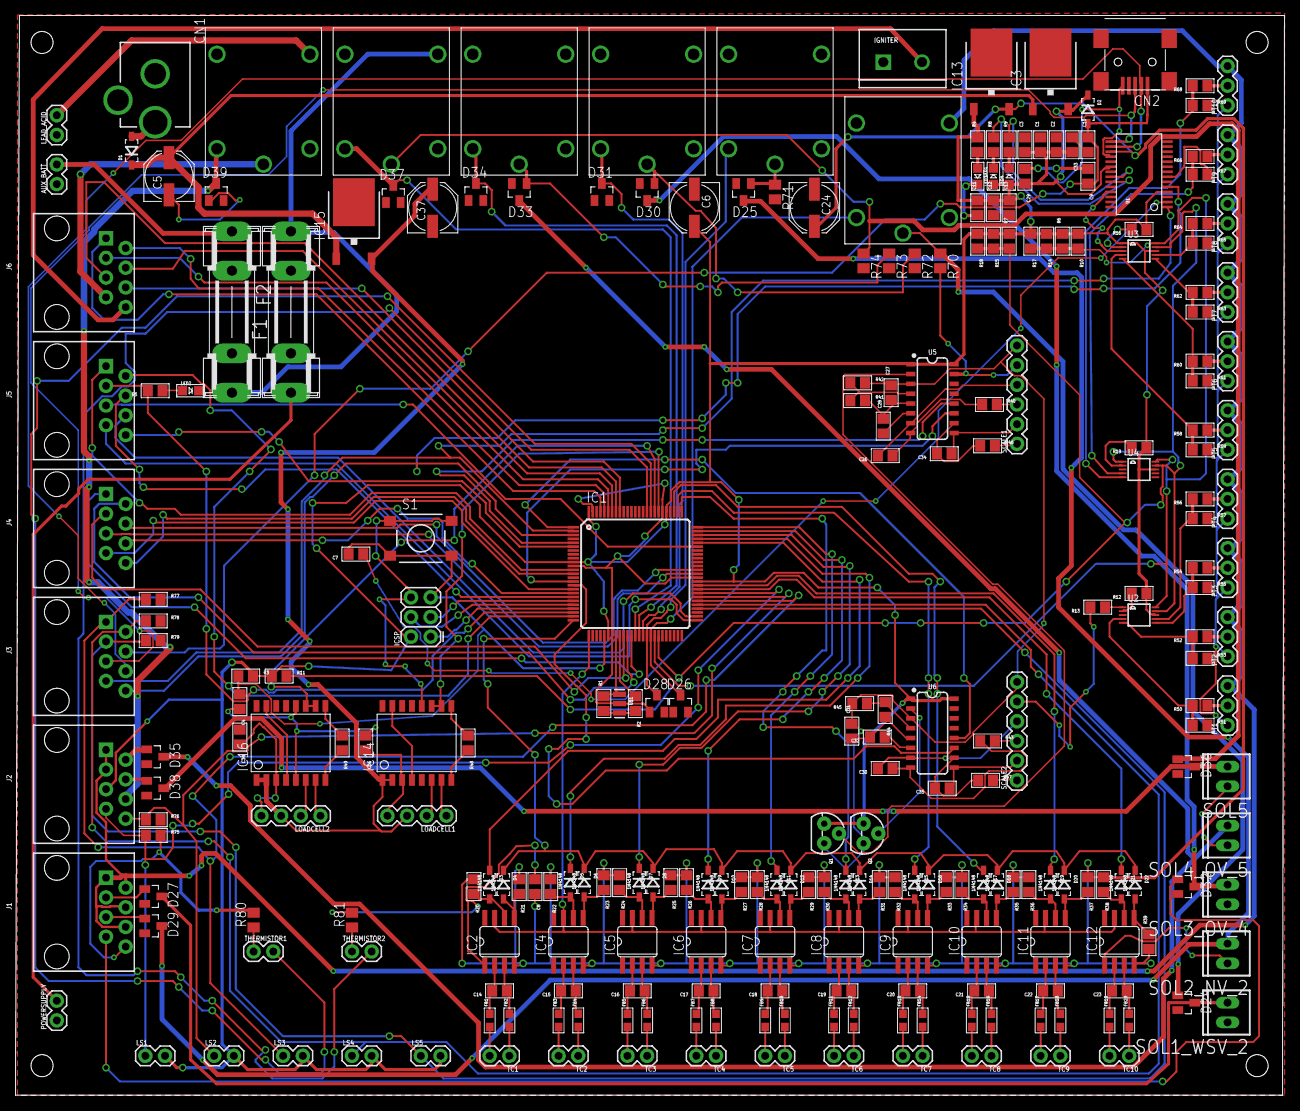
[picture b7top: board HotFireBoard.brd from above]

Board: 2 copper layers, 163.8 x 139.4 mm, 263 parts (0 on the bottom side), 220 nets.
